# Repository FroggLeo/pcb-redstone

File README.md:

# PCB Redstone
Minecraft redstone but with real PCB tiles, connecting magnetically and functions just like the game!

## Features:
- RP2040 microcontroller
- 40*40mm compact design 
- Dual 4 pin magentic pogo pins to connect on any side (2 pins per channel)
- Lots of toggleable LEDs to match block functions!
- Simulate Java or Bedrock redstone mechanics
- Program with 2.54mm holes using SWD
- Communicate with 2 GPIO inputs/outputs
- Inject 12v sources to any tiles and power all the blocks

## Current blocks:
### Redstone Dust

### Redstone Block

### Redstone Comparator

### Redstone Lamp & Copper Lamp

### Redstone Repeater

## Firmware:
[Firmware for the PCB redstone can be found here!](https://github.com/Hashikono/recom-simulation)

## Honorable mentions:
- KiCad
- Mouser library importer
- Little bits (initial inspiration!)
- Kaylee [@kaylz-d](https://github.com/kaylz-d)
- Hack Club Blueprint

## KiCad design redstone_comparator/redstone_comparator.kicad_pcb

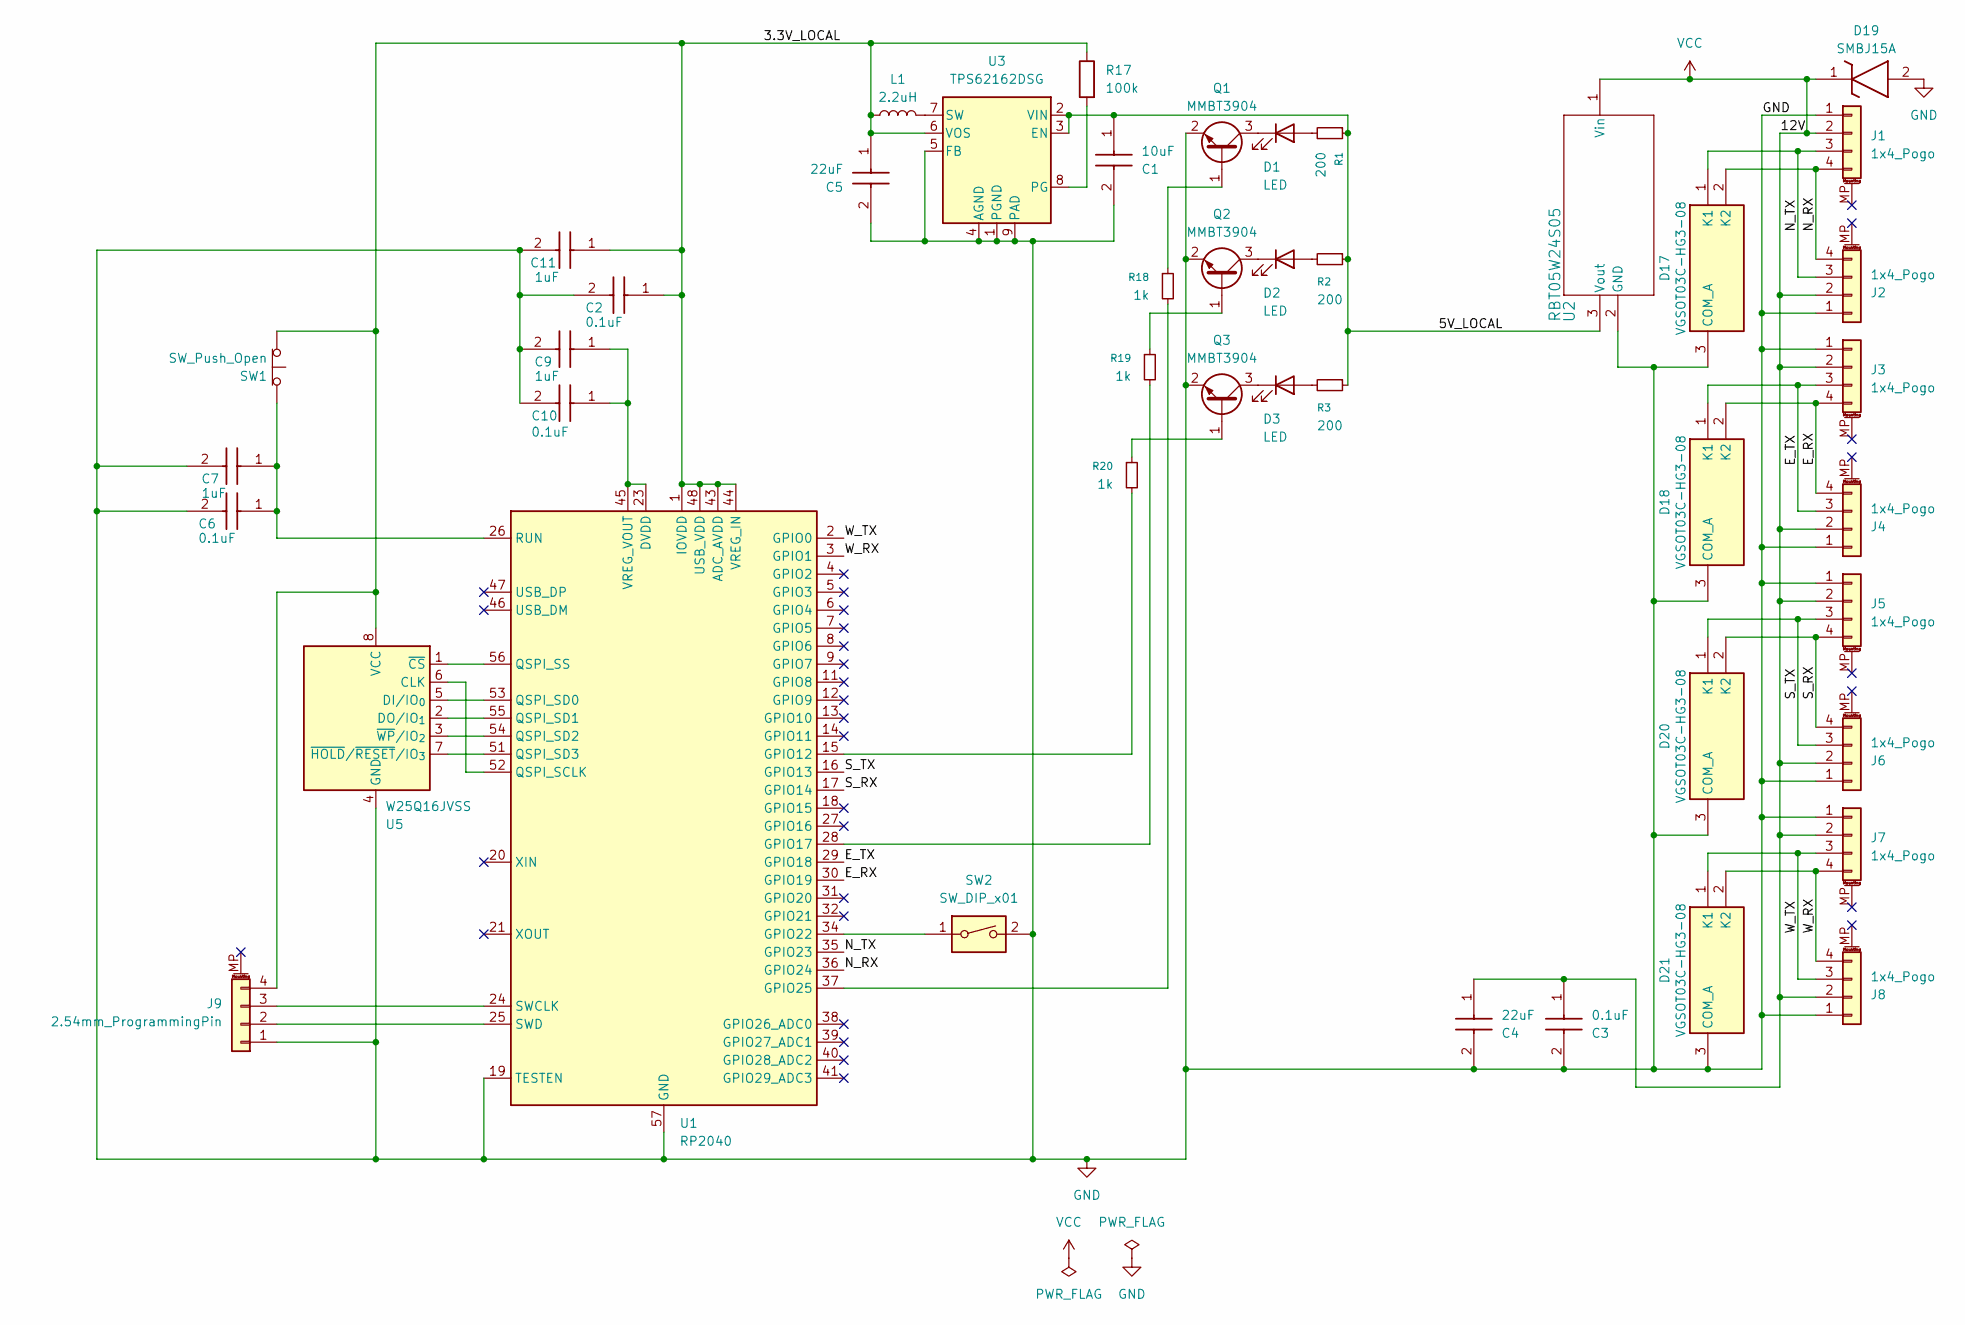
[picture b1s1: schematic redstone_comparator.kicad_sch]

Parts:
C1: 10uF; CAPC1005X70N; Manufacturer_Part_Number GRM155R60J106ME18D
C2, C3, C6, C10: 0.1uF; CAPC2012X140N; Manufacturer_Part_Number C0805F104K1RACAUTO
C4, C5: 22uF; GRM18x; Manufacturer_Part_Number GRM188C81A226ME01D
C7, C9, C11: 1uF; CAPC0603X33N; Manufacturer_Part_Number GRM033D70E105ME15D; Mouser Part Number 81-GRM033D70E105ME5D
D1, D2, D3: LED; LED_D3.0mm
D17, D18, D20, D21: VGSOT03C-HG3-08; SOT95P248X115-3N; Manufacturer_Part_Number VGSOT03C-HG3-08
D19: SMBJ15A; DIOM5436X244N; Manufacturer_Part_Number SMBJ15A; Mouser Part Number 78-SMBJ15A
J1, J2, J3, J4, J5, J6, J7, J8: 1x4_Pogo; PinSocket_1x04_P2.54mm_Vertical
J9: 2.54mm_ProgrammingPin; PinSocket_1x04_P2.54mm_Vertical
L1: 2.2uH; LCENA2016MKT2R2M0NK
Q1, Q2, Q3: MMBT3904; SOT-23
R1, R2, R3: 200; CRCW1210200RJNEAIF
R17: 100k; TNPW0805100KFHEA
R18, R19, R20: 1k; ERJ-UP6D1001V
SW1: SW_Push_Open; SW_TH_Tactile_Omron_B3F-100x
SW2: SW_DIP_x01; 416131160801
U1: RP2040; QFN-56-1EP_7x7mm_P0.4mm_EP3.2x3.2mm
U2: RBT05W24S05; RBT10W24S05_XPP_XPR
U3: TPS62162DSG; WSON-8-1EP_2x2mm_P0.5mm_EP0.9x1.6mm_ThermalVias
U5: W25Q16JVSS; SOIC-8_5.3x5.3mm_P1.27mm

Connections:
/3.3V_LOCAL: C2.1, C5.1, C11.1, J9.4, L1.1, R17.1, SW1.1 (A), U1.1 (IOVDD), U1.10 (IOVDD), U1.22 (IOVDD), U1.33 (IOVDD), U1.42 (IOVDD), U1.43 (ADC_AVDD), U1.44 (VREG_IN), U1.48 (USB_VDD), U1.49 (IOVDD), U3.6 (VOS), U5.8 (VCC); also elsewhere on the board
/5V_LOCAL: C1.1, R1.1, R2.1, R3.1, U2.3 (Vout), U3.2 (VIN), U3.3 (EN)
/E_RX: D18.2 (K2), J3.4, J4.4, U1.30 (GPIO19)
/E_TX: D18.1 (K1), J3.3, J4.3, U1.29 (GPIO18)
/N_RX: D17.2 (K2), J1.4, J2.4, U1.36 (GPIO24)
/N_TX: D17.1 (K1), J1.3, J2.3, U1.35 (GPIO23)
/S_RX: D20.2 (K2), J5.4, J6.4, U1.17 (GPIO14)
/S_TX: D20.1 (K1), J5.3, J6.3, U1.16 (GPIO13)
/W_RX: D21.2 (K2), J7.4, J8.4, U1.3 (GPIO1)
/W_TX: D21.1 (K1), J7.3, J8.3, U1.2 (GPIO0)
GND: C1.2, C2.2, C3.2, C4.2, C5.2, C6.2, C7.2, C9.2, C10.2, C11.2, D17.3 (COM_A), D18.3 (COM_A), D19.2 (A), D20.3 (COM_A), D21.3 (COM_A), J1.1, J2.1, J3.1, J4.1, J5.1, J6.1, J7.1, J8.1, J9.1, Q1.2 (E), Q2.2 (E), Q3.2 (E), SW2.2, U1.19 (TESTEN), U1.57 (GND), U2.2 (GND), U3.1 (PGND), U3.4 (AGND), U3.5 (FB), U3.9 (PAD), U5.4 (GND); also elsewhere on the board
unnamed: D1.2 (A), R1.2
unnamed: D1.1 (K), Q1.3 (C)
unnamed: D2.2 (A), R2.2
unnamed: D2.1 (K), Q2.3 (C)
unnamed: D3.2 (A), R3.2
unnamed: D3.1 (K), Q3.3 (C)
unnamed: J9.2, U1.25 (SWD)
unnamed: J9.3, U1.24 (SWCLK)
unnamed: Q1.1 (B), R18.1
unnamed: Q2.1 (B), R19.1
unnamed: Q3.1 (B), R20.1
unnamed: C6.1, C7.1, SW1.2 (B), U1.26 (RUN)
unnamed: R20.2, U1.15 (GPIO12)
unnamed: R19.2, U1.28 (GPIO17)
unnamed: SW2.1, U1.34 (GPIO22)
unnamed: R18.2, U1.37 (GPIO25)
unnamed: U1.52 (QSPI_SCLK), U5.6 (CLK)
unnamed: U1.53 (QSPI_SD0), U5.5 (DI/IO_{0})
unnamed: U1.55 (QSPI_SD1), U5.2 (DO/IO_{1})
unnamed: U1.54 (QSPI_SD2), U5.3 (~WP/IO_{2})
unnamed: U1.51 (QSPI_SD3), U5.7 (~HOLD/~RESET/IO_{3})
unnamed: U1.56 (QSPI_SS), U5.1 (~CS)
unnamed 33: C9.1, C10.1, U1.23 (DVDD), U1.45 (VREG_VOUT), U1.50 (DVDD); also elsewhere on the board
unnamed: R17.2, U3.8 (PG)
unnamed: L1.2, U3.7 (SW)
VCC: C3.1, C4.1, D19.1 (K), J1.2, J2.2, J3.2, J4.2, J5.2, J6.2, J7.2, J8.2, U2.1 (Vin)

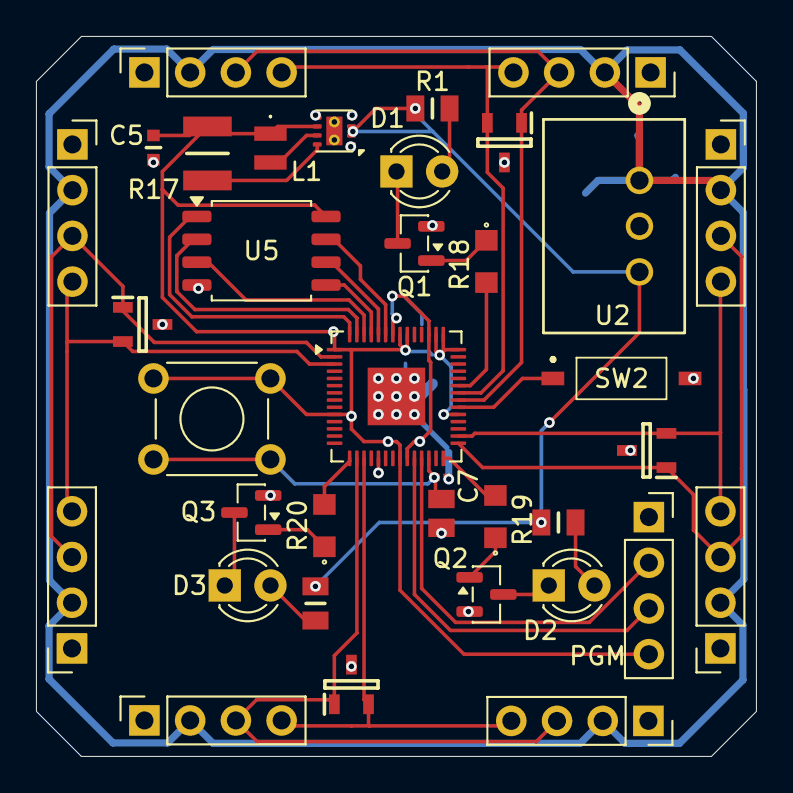
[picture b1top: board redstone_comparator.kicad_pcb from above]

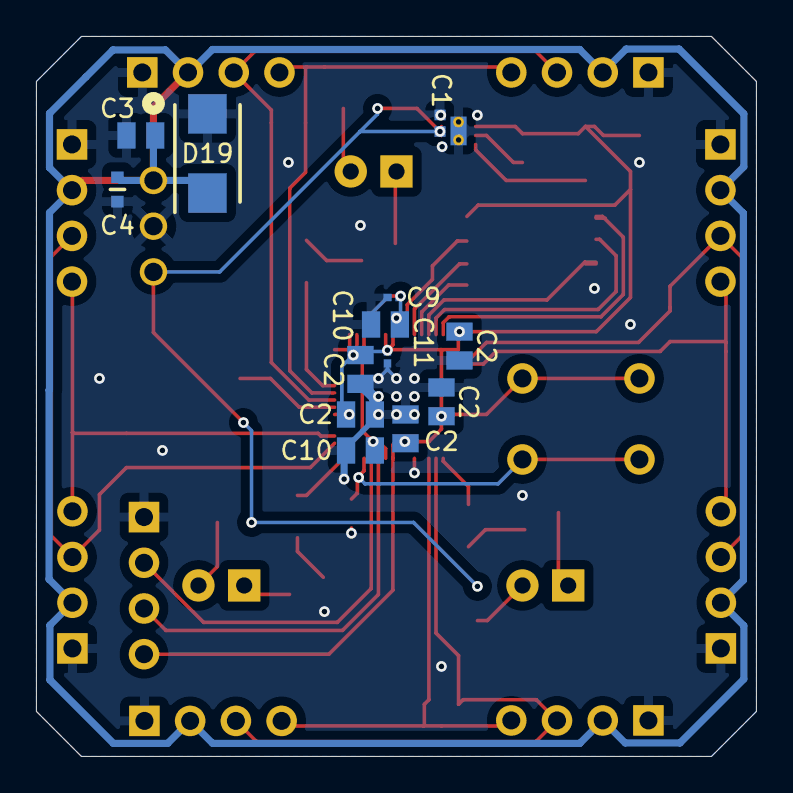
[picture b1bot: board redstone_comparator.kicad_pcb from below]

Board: 2 copper layers, 40.0 x 40.0 mm, 49 parts (13 on the bottom side), 37 nets.

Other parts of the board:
C2#2, C2#3, C2#4, C2#5, C10#2: 0.1uF; CAPC2012X140N

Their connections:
/3.3V_LOCAL: C2#2.1, C2#3.1, C2#4.1, C2#5.1; also elsewhere on the board
GND: C2#2.2, C2#3.2, C2#4.2, C2#5.2, C10#2.2; also elsewhere on the board
unnamed 33: C10#2.1; also elsewhere on the board

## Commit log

2025-11-06 add redstone dust files
2025-11-06 add more leds
2025-11-06 add tx rx wiring, add flash memory
2025-11-06 connect flash memory
2025-11-07 add gitignore
2025-11-07 add gitignore entries for kicad
2025-11-07 rename redstone to redstone_dust
2025-11-07 add resistors with proper values
2025-11-07 add tvs diode and reorganize wiring
2025-11-07 add tps diodes for rx tx
2025-11-07 add decoupling capacitors
2025-11-07 add programming pins
2025-11-07 add no connect flags to unconnected pins
2025-11-07 run erc and fix some errors
2025-11-10 add decoupling capacitors for rp2040
2025-11-10 add some symbol footprints
2025-11-10 add footprint for pogo pins
2025-11-10 switch GND and VCC pins to match pcb footprint
2025-11-11 add basic pcb layout, fix disconnected ground net
2025-11-13 remove some unecessary capacitors
2025-11-13 add very bad traces, most likely will redo pcb layout
2025-11-13 snapshot before removing all traces and restarting layout
2025-11-13 remove all traces to restart layout
2025-11-13 redoing pcb layout with new approach
2025-11-13 move pogo pin footprints over to new layout
2025-11-13 connect more traces, progress is well
2025-11-13 add more traces, almost done
2025-11-14 add remaining tracks except ground
2025-11-14 move pins closer to the corners, create ground plane fill on bottom
2025-11-14 reasolve all drc check errors, todo resolve warnings
2025-11-14 fix front side silkscreens
2025-11-16 change programming pin 4 to 3.3v
2025-11-17 fix all silkscreen drc errors
2025-11-17 finalize redstone dust
2025-11-17 duplicate redstone dust file and modify to fit redstone block
2025-11-18 finalize redstone block and duplicate redstone dust to create lamp
2025-11-18 remove all unecessary components in schematic
2025-11-18 finalize redstone lamp design
2025-11-18 clean up and organize redstone dust schematic
2025-11-18 remove unecessary silkscreen markings on redstone block
2025-11-18 add dip switch to schematic, todo update pcb design
2025-11-19 remove dip switch, cannot find one that fits in board space
2025-11-19 duplicate redstone lamp project for redstone repeator
2025-11-19 add 4 way switch for repeater
2025-11-19 switch redstone dust transistor to a much smaller one, todo switch transistors on other tiles as well
2025-11-19 switch redstone lamp transistor to mmbt3904
2025-11-19 move reset buttom and add dip switch
2025-11-20 add four individually controlled leds for repeater, small adjustments for redstone dust
2025-11-21 reorganize pcb layout for redstone repeater
2025-11-28 finalize schematic and finish layout of pcb
2025-11-28 finish wiring layout
2025-11-28 run drc, fix silkscreen, fix drc errors
2025-11-29 duplicate redstone dust for comparator
2025-11-29 finalize initial comparator design
2025-11-29 finish routing all connections, todo align components and make it symmetric
2025-12-06 include csv for BOM
2025-12-06 add BOMs for all blocks
2025-12-08 generate gerber files for all blocks
2025-12-08 organize all gerber files
